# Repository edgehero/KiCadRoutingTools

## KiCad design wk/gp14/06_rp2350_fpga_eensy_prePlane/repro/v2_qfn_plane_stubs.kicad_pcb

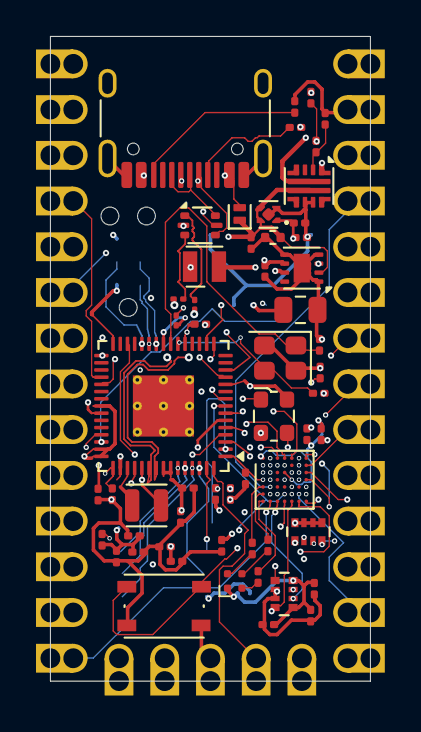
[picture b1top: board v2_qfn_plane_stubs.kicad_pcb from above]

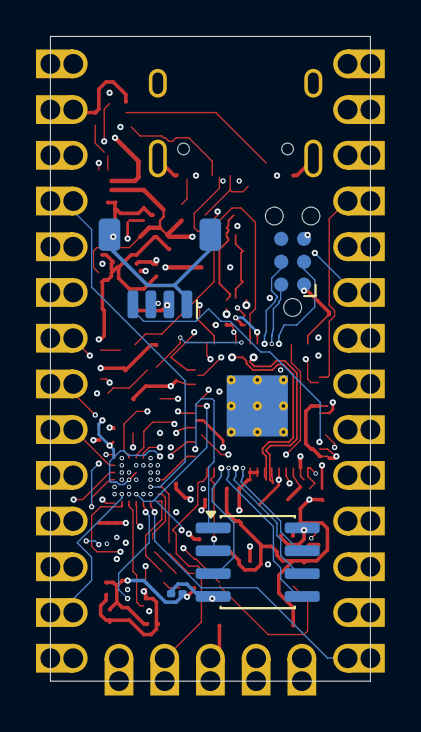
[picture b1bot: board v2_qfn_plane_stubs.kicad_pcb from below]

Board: 6 copper layers, 17.8 x 35.8 mm, 61 parts (4 on the bottom side), 74 nets.

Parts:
C1, C2, C3, C7, C8, C9, C10, C11, C12, C17, C18, C20, C21, C23, C24, C25, C28, C29, C30: 1uF; C_0201_0603Metric
C5, C13, C16, C19, C22: 4.7uF; C_0201_0603Metric
C6: 4.7uF; amemb-C_0201_0603Metric_L
C14, C15: 18pF; C_0201_0603Metric
C26: 10uF; amemb-C_0402_1005Metric_L
C27: 22uF; C_0805_2012Metric
D1: LED; LED_Wurth_150044M155260
D2: D_Schottky_Small; D_SOD-882
J1: USB_C_Receptacle_USB2.0_14P; USB_C_Receptacle_HRO_TYPE-C-31-M-12-Edge_Silkscreen_Removed
J2: Conn_ARM_SWD_TagConnect_TC2030-NL; Tag-Connect_TC2030-IDC-NL_2x03_P1.27mm_Vertical
J3: Conn_01x04_MountingPin; JST_SH_SM04B-SRSS-TB_1x04-1MP_P1.00mm_Horizontal
L1: 3.3uH; L_Wuerth_PMCI-201610
L2: 2.2uH; L_Wurth_WE-LQSH-2010
R1, R2: 5.1kR; R_0201_0603Metric
R3: 33R; R_0201_0603Metric
R4, R5: 27R; amemb-R_0201_0603Metric_L
R6: 1MR; R_0201_0603Metric
R7: 680R; R_0201_0603Metric
R8: 360R; R_0201_0603Metric
R9: 300R; R_0201_0603Metric
R11: 470kR; R_0201_0603Metric
R12: 18.7kR; R_0201_0603Metric
R13: 46.4kR; R_0201_0603Metric
RN1, RN2: 10kR; R_Array_Convex_4x0402
SW1: SKRPADE010; SW_Push_1P1T_NO_Vertical_Wuerth_434133025816
U1: APS1604M-SQR-SN; SOIC-8_3.9x4.9mm_P1.27mm
U2: T8F49I2X; amemb-WLCSP-49_3x3mm_Layout7x7_P0.4mm_Ball0.25mm
U3: USBLC6-2P6; SOT-666
U4: TPS7A2011DQN; Texas_X2SON-4_1x1mm_P0.65mm
U5: LM73100RPWR; Texas_Instruments-VQFN-HR-10_2x2mm_P0.475mm
U6: RP2354A; QFN-60-1EP_7x7mm_P0.4mm_EP3.4x3.4mm_ThermalVias
U7: TPS62162DSG; WSON-8-1EP_2x2mm_P0.5mm_EP0.9x1.6mm
U8: Teensy4.0; Teensy40
Y1: 12MHZ; Crystal_SMD_2520-4Pin_2.5x2.0mm
Y2: 32MHz; Oscillator_SMD_ECS_2520MV-xxx-xx-4Pin_2.5x2.0mm

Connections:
+1V1: C3.1, C16.1, C17.1, C18.1, U2.A1 (VCCA_PLL), U2.C4 (VCC), U2.D5 (VCC), U4.1 (OUT), U7.3 (EN)
+3V3: C2.1, C7.1, C8.1, C9.1, C10.1, C11.1, C12.1, C13.1, C19.1, C20.1, C21.1, C22.1, C23.1, C24.1, C25.1, C27.1, D1.1 (A), J2.1 (VCC), J3.2, L2.2, R3.2, RN1.5 (R4.2), RN1.6 (R3.2), RN1.7 (R2.2), RN1.8 (R1.2), RN2.5 (R4.2), RN2.8 (R1.2), U1.8 (VDD), U2.B2 (VCCIO1B), U2.B6 (VCCIO2A), U2.D1 (VCCIO1A), U2.F7 (VCCIO2B), U6.1 (IOVDD), U6.11 (IOVDD), U6.20 (IOVDD), U6.30 (IOVDD), U6.38 (IOVDD), U6.44 (ADC_AVDD), U6.45 (IOVDD), U6.49 (VREG_VIN), U6.53 (USB_OTP_VDD), U6.54 (QSPI_IOVDD), U7.6 (VOS), U8.16 (3V3), U8.31 (3V3), Y2.4 (VDD)
/PIO22: U6.34 (GPIO22), U8.4 (PIN2)
/PIO23: U6.35 (GPIO23), U8.5 (PIN3)
/Power Supply and USB/D+: R4.1, U3.1 (I/O1)
/Power Supply and USB/D-: R5.1, U3.3 (I/O2)
/RP2354A/1V1: C6.1, C28.1, C29.1, C30.1, L1.1, U6.6 (DVDD), U6.23 (DVDD), U6.39 (DVDD), U6.50 (VREG_FB)
/RP2354A/FPGA.CLK: U2.F3 (GPIOL_02_CCK), U6.4 (GPIO2)
/RP2354A/FPGA.DONE: RN2.1 (R1.1), U2.F4 (CDONE), U6.8 (GPIO5)
/RP2354A/FPGA.MOSI: U2.F2 (GPIOL_04_CDI0), U6.5 (GPIO3)
/RP2354A/FPGA.OSC_EN: R6.1, U6.31 (GPIO19), Y2.1 (Tri-State)
/RP2354A/FPGA.~CS: RN2.6 (R3.2), U2.G3 (~GPIOL_01_SS), U6.3 (GPIO1)
/RP2354A/FPGA.~RESET: RN2.7 (R2.2), U2.G4 (~CRESET), U6.7 (GPIO4)
/RP2354A/FPGA.~STATUS: U2.A4 (GPIOL_21_~STATUS), U6.9 (GPIO6)
/RP2354A/ON/OFF: U6.28 (GPIO17), U8.19 (ON/OFF)
/RP2354A/PROGRAM: U6.60 (QSPI_SS), U8.18 (PROGRAM)
/RP2354A/QSPI_PSRAM_~CS: U1.1 (~CE), U6.2 (GPIO0)
/RP2354A/RP.UART0_RX: U6.17 (GPIO13), U8.10 (PIN8)
/RP2354A/RP.UART0_TX: U6.16 (GPIO12), U8.9 (PIN7)
/RP2354A/RP.UART1_RX: U6.12 (GPIO8), U8.2 (PIN0)
/RP2354A/RP.UART1_TX: U6.13 (GPIO9), U8.3 (PIN1)
/RP2354A/SCL: J3.4, U6.43 (GPIO29/ADC3)
/RP2354A/SDA: J3.3, U6.42 (GPIO28/ADC2)
/RP2354A/SWCLK: J2.4 (SWCLK), U6.24 (SWCLK)
/RP2354A/SWDIO: J2.2 (SWDIO), U6.25 (SWDIO)
/RP2354A/USB_D+: R4.2, U6.52 (USB_DP)
/RP2354A/USB_D-: R5.2, U6.51 (USB_DM)
/T8F49I2X/B: R9.2, U2.G1 (GPIOL_05_CDI5)
/T8F49I2X/G: R8.2, U2.F1 (GPIOL_06_CDI1)
/T8F49I2X/PIN.4: U2.A5 (GPIOR_05), U8.6 (PIN4)
/T8F49I2X/PIN.5: RN1.4 (R4.1), U2.D7 (GPIOR_17_CTRL6_CBUS2), U8.7 (PIN5)
/T8F49I2X/PIN.6: RN1.3 (R3.1), U2.C7 (GPIOR_16_CTRL7_CBUS1), U8.8 (PIN6)
/T8F49I2X/PIN.9: RN1.2 (R2.1), U2.D6 (GPIOR_15_CBUS0), U8.11 (PIN9)
/T8F49I2X/PIN.10: RN1.1 (R1.1), U2.G7 (~GPIOR_37_TEST), U8.12 (PIN10)
/T8F49I2X/PIN.11: RN2.4 (R4.1), U2.G5 (GPIOR_34_CSI), U8.13 (PIN11)
/T8F49I2X/PIN.12: U2.G2 (GPIOL_03_CDI4), U8.14 (PIN12)
/T8F49I2X/PIN.13: U2.F5 (GPIOR_24), U8.20 (PIN13)
/T8F49I2X/PIN.14: U2.F6 (GPIOR_26_CBSEL0), U8.21 (PIN14)
/T8F49I2X/PIN.15: U2.E5 (GPIOR_23_CTRL4), U8.22 (PIN15)
/T8F49I2X/PIN.16: U2.C6 (GPIOR_13), U8.23 (PIN16)
/T8F49I2X/PIN.17: U2.B3 (GPIOL_16_CLK2), U8.24 (PIN17)
/T8F49I2X/PIN.18: U2.B7 (GPIOR_10), U8.25 (PIN18)
/T8F49I2X/PIN.19: U2.A7 (GPIOR_07), U8.26 (PIN19)
/T8F49I2X/PIN.20: U2.A3 (GPIOL_18_CTRL2), U8.27 (PIN20)
/T8F49I2X/PIN.21: U2.C2 (GPIOL_12_CTRL0), U8.28 (PIN21)
/T8F49I2X/PIN.22: U2.D2 (GPIOL_11_CDI3), U8.29 (PIN22)
/T8F49I2X/PIN.23: U2.E2 (GPIOL_09_CDI2), U8.30 (PIN23)
/T8F49I2X/R: R7.2, U2.E1 (GPIOL_10_CDI7)
/VIN: R11.1, U5.5 (IN), U8.33 (VIN)
GND: C1.2, C2.2, C3.2, C5.2, C6.2, C7.2, C8.2, C9.2, C10.2, C11.2, C12.2, C13.2, C14.2, C15.2, C16.2, C17.2, C18.2, C19.2, C20.2, C21.2, C22.2, C23.2, C24.2, C25.2, C26.2, C27.2, C28.2, C29.2, C30.2, J1.A1 (GND), J1.A12 (GND), J1.B1 (GND), J1.B12 (GND), J1.SH (SHIELD), J2.5 (GND), J3.1, J3.MP (MountPin), R1.2, R2.2, R6.2, R13.2, RN2.2 (R2.1), RN2.3 (R3.1), SW1.2, U1.4 (VSS), U2.A2 (GND), U2.A6 (GND), U2.B1 (GND), U2.C1 (GND), U2.C5 (GND), U2.D4 (GND), U2.E7 (GND), U3.2 (GND), U4.2 (GND), U4.5 (Pad), U5.8 (GND), U5.9 (IMON), U6.47 (VREG_PGND), U6.61 (GND), U7.1 (PGND), U7.4 (AGND), U7.5 (FB), U7.9 (PAD), U8.1 (GND), U8.17 (GND), U8.32 (GND), Y1.2 (G), Y1.4 (G), Y2.2 (GND)
unnamed: D1.4 (BK), R9.1
unnamed: D1.3 (GK), R8.1
unnamed: D1.2 (RK), R7.1
unnamed: D2.2 (A), J1.A4 (VBUS), J1.A9 (VBUS), J1.B4 (VBUS), J1.B9 (VBUS)
unnamed: C1.1, C26.1, D2.1 (K), U3.5 (VBUS), U4.3 (EN), U4.4 (IN), U5.6 (OUT), U7.2 (VIN)
unnamed: J1.A5 (CC1), R1.1
unnamed: J1.B5 (CC2), R2.1
unnamed: J1.A6 (D+), J1.B6 (D+), U3.6 (I/O1)
unnamed: J1.A7 (D-), J1.B7 (D-), U3.4 (I/O2)
unnamed: J2.3 (~RESET), U6.26 (RUN)
unnamed: U1.6 (SCLK), U6.56 (QSPI_SCLK)
unnamed: U1.3 (SIO2), U6.58 (QSPI_SD2)
unnamed: U1.7 (SIO3), U6.55 (QSPI_SD3)
unnamed: U1.5 (SI/SIO0), U6.57 (QSPI_SDO)
unnamed: U1.2 (SO/SIO1), U6.59 (QSPI_SD1)
unnamed: U2.B4 (GPIOL_20_PLLIN), Y2.3 (OUT)
unnamed: SW1.1, U2.G6 (GPIOR_35_CSO)
unnamed: R11.2, R12.1, U5.1 (EN/UVLO)
unnamed: R12.2, R13.1, U5.2 (OVLO)
unnamed: C5.1, R3.1, U6.46 (VREG_AVDD)
unnamed: L1.2, U6.48 (VREG_LX)
unnamed: C14.1, U6.21 (XIN), Y1.3
unnamed: C15.1, U6.22 (XOUT), Y1.1
unnamed: L2.1, U7.7 (SW)

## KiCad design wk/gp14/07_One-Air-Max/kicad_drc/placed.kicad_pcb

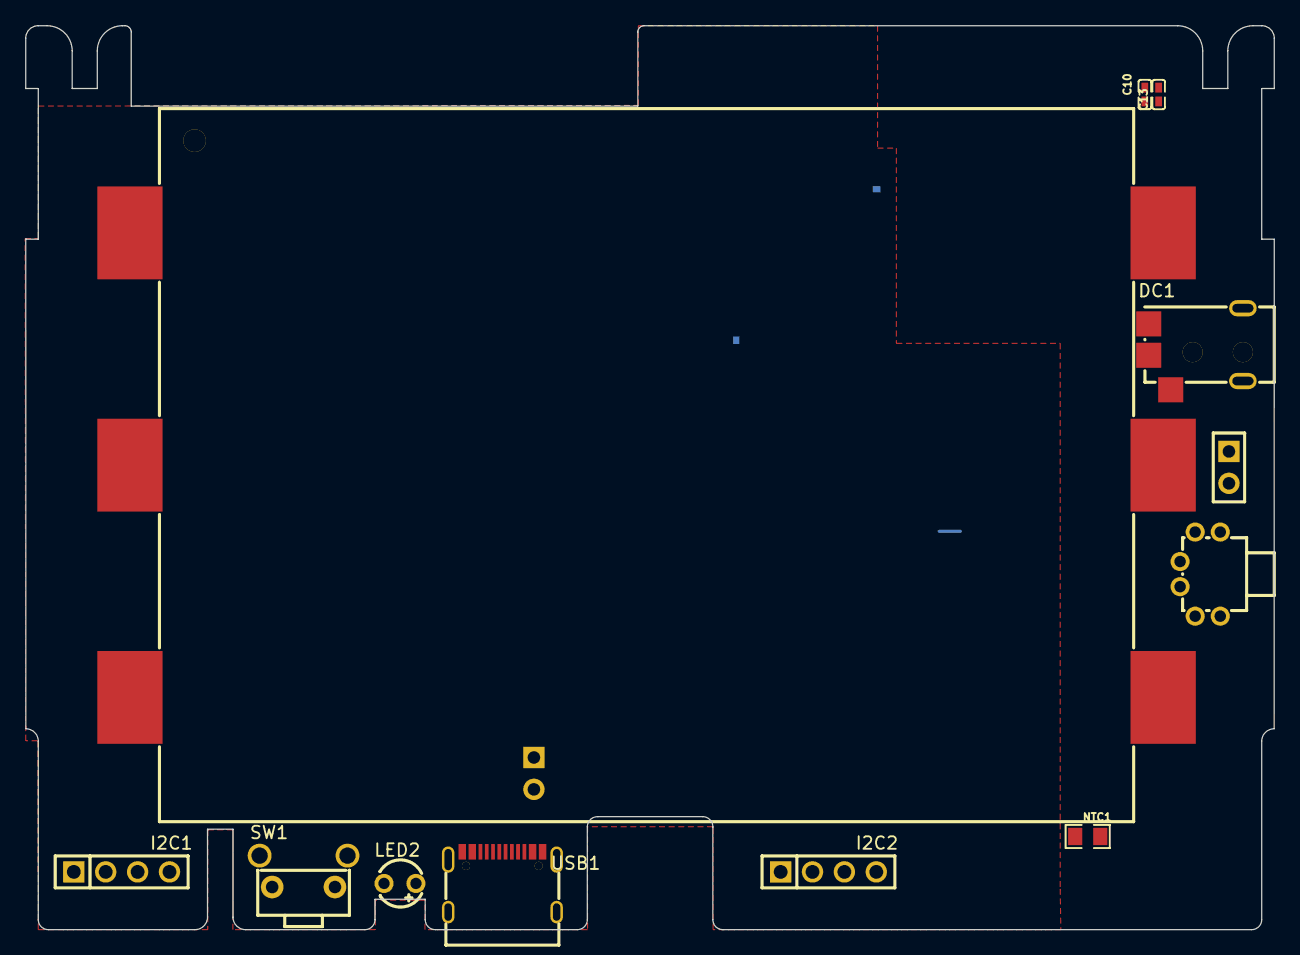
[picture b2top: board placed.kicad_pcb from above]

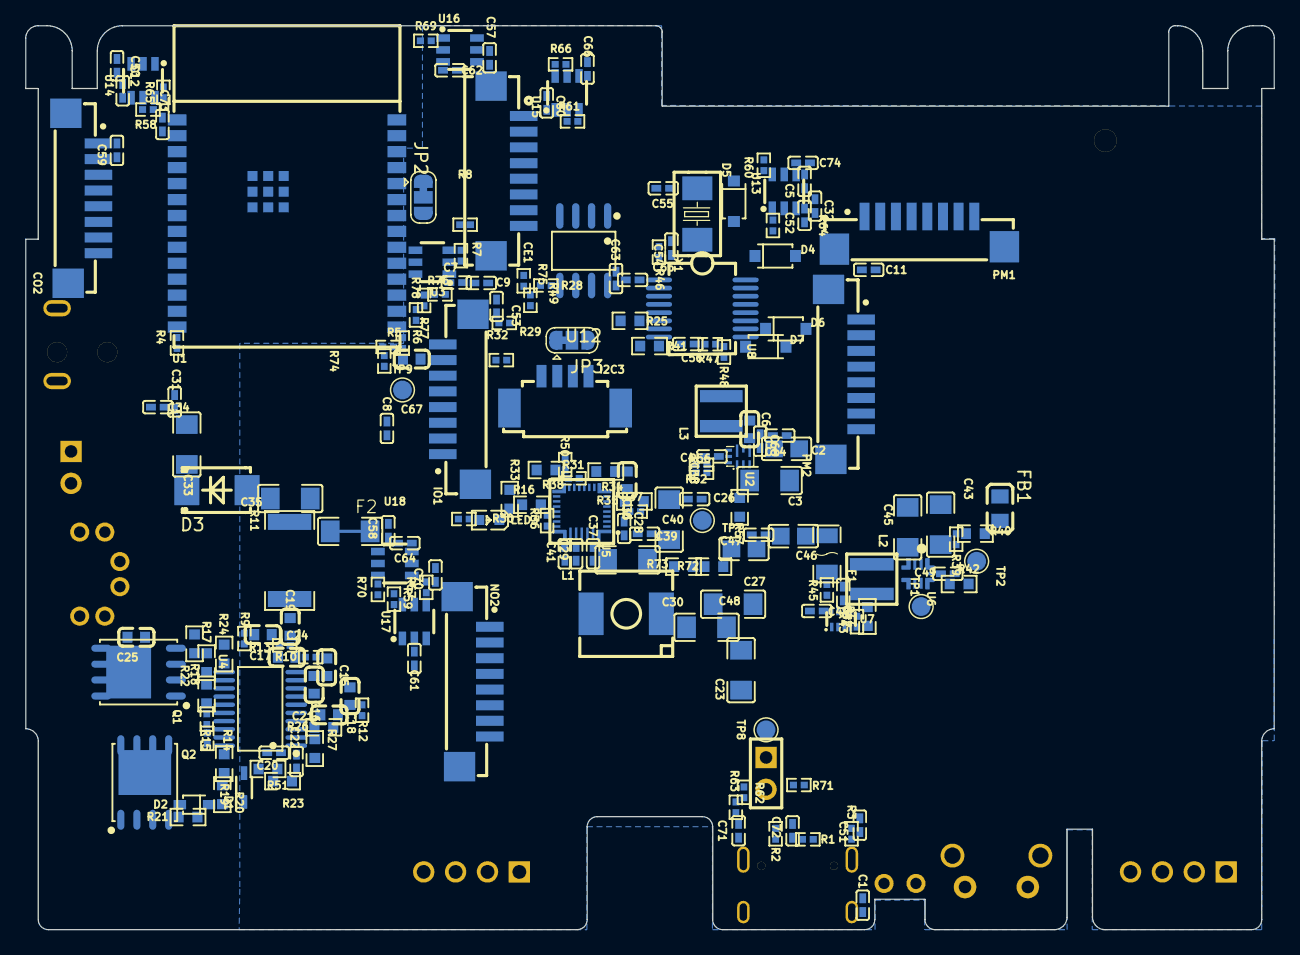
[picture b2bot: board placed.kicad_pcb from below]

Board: 4 copper layers, 99.5 x 72.0 mm, 204 parts (192 on the bottom side), 120 nets, no tracks yet.

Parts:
BAT1: BH-18650-B5BA016; BAT-SMD_BH-18650-B5BA016
Battery1: ZX-PM2.54-1-2PY; HDR-TH_2P-P2.54-V-F
C1, C5, C7, C9, C10, C11, C12, C13, C26, C31, C34, C37, C39, C42, C44, C47, C50, C51, C52, C53, C56, C63, C65, C70: 0.1uF; C0402
C2: 10uF/25V; C0805
C3: 22uF/16V; C1206
C4, C49: 3.3nF; C0402
C6: 22uF; C0603
C8: 10nF; C0402
C14, C57, C58, C68, C74: 22uF; C0402
C15, C16, C17, C18, C19, C21, C24, C25: 0.1uF/50V; C0603
C20, C22: 1uF/50V; C0402
C23, C27, C30, C33, C35, C38, C40, C43, C45: 10uF; C1206
C28, C29: 47nF; C0402
C32, C59, C60, C61, C62, C64: 2.2uF; C0402
C36: 4.7uF; C0603
C41, C71, C72: 1nF; C0402
C46, C48: 22uF; C0805
C54, C55: 22pF_NM; C0402
C66, C73: 1uF; C0402
C67: 500pF; C0603
CE1: HC-1.25-8PWT; CONN-SMD_HC-1.25-8PWT
CO2: HC-1.25-8PLT; CONN-SMD_8P-P1.25_HC-1.25-8PLT
D1: BAS16J_135; SOD2512X80N
D2: MMSZ5246BS-7-F; SOD-323_L1.8-W1.3-LS2.5-RD
D3: SMBJ24A_C908801; SMB_L4.4-W3.6-LS5.3-RD
D4, D5, D6, D7: B5817W_C7420328; SOD-123_L2.7-W1.6-LS3.7-FD
DC1: DC-045A-13A; DC-IN-SMD_DC-045A-13A
F1: 2A-16V; F1206
F2: Fuse 5A; PCB_fuse
FB1: PBY201209T-601Y-N; L0805
I2C1, I2C2: Conn_01x04; HDR-TH_4P-P2.54-V-F
I2C3: 1.25-4PWB; CONN-SMD_1.25-4PWB
IO1: HC-1.25-8PLT; CONN-SMD_8P-P1.25_HC-1.25-8PLT
JP2, JP3: SolderJumper_3_Bridged12; SolderJumper-3_P1.3mm_Bridged12_RoundedPad1.0x1.5mm
L1: SPM6530T-1R0M120; IND-SMD_L7.1-W6.5-P5.60
L2: XGL4020-102MEC; IND-SMD_L4.0-W4.0_XAL4030-332MEC
L3: YSMC0420V-1R0M; IND-SMD_L4.0-W4.0_XGL4020
LED2: XL-304UBC; LED-TH_BD3.8-P2.54-FD_BLUE
LED3: FC-DA1608HRK-620D; LED0603-RD_RED
NO2: HC-1.25-8PLT; CONN-SMD_8P-P1.25_HC-1.25-8PLT
NTC1: KNTC0805/10KF3950; R0805
PM1, PM2: HC-1.25-8PLT; CONN-SMD_8P-P1.25_HC-1.25-8PLT
PWR_SW1: TK-6580A8-1; SW-TH_TK-6580A8-1
Q1, Q2: CSD18534Q5A; PQFN-8_L5.8-W4.9-P1.27-LS6.0-BL
R1, R2, R48: 5.1K; R0402
R3, R6, R31, R37: 100K; R0402
R4, R5, R8, R28, R29, R30, R32, R45, R47, R49, R50, R58, R59, R60, R61, R64, R65, R66, R67, R69, R70, R74, R75, R76, R77, R78: 10K; R0402
R7: 51K; R0402
R9, R12, R14, R15: 1K; R0402
R10, R13, R36: 100; R0402
R11: 10m / 1W; R2512
R16: 10.5K; R0603
R17, R19: 5.1K; R0603
R18: 10M; R0603
R20: 1M; R0603
R21: 3M; R0603
R22: 10K; R0603
R23, R25, R26, R27, R33, R41, R51, R72, R73: 0; R0603
R24: 470K; R0603
R34: 5.23K; R0603
R35: 255K; R0603
R38: 30.1K; R0603
R39: 200K; R0402
R40: 27K; R0603
R42, R57: 7.15K; R0603
R43: 16.9K; R0402
R44: 5K; R0603
R46: 1M; R0402
R52: 113k; R0402
R56: 24.9k; R0402
R62, R63: 22; R0402
R71: 210; R0402
SW1: TS-1096-A1B2-D2; KEY-TH_TS-1096-A1B2-D2
Solarpower1: ZX-PM2.54-1-2PY; HDR-TH_2P-P2.54-V-F
TP1, TP2, TP7, TP8, TP9: T_PG; TestPoint_Pad_D1.5mm
U1: ESP32-C6-WROOM-1-N8; WIRELM-SMD_ESP32-C6-WROOM-1
U2: TPS62902RPJR; VQFN-HR-9_L2.0-W1.5-P0.50-TL
U3: TPL5010DDCR; SOT-23-6_L2.9-W1.6-P0.95-LS2.8-BR
U4: BQ7790512PWR; TSSOP-20_L6.5-W4.4-P0.65-LS6.4-BL
U5: BQ25672RQMR; VQFN-29_L4.0-W4.0-P0.40-BL
U6: TPS62903QRYTRQ1_C20345985; VQFNHR-9_L2.2-W2.0_TPS62993QRYTRQ1
U7: TPS2117DRLR_C22399676; SOT-583-8_L2.1-W1.2-P0.50-LS1.6-BL
U8: WK2132-ISSG; SSOP-16_L7.2-W5.3-P0.65-LS7.8-BL
U12: AT24CM02-SSHD-B; SOIC-8_L4.9-W3.9-P1.27-LS6.0-BL
U13, U14, U15, U16, U17, U18: TPS27081ADDCR; SOT-23-6_L2.9-W1.6-P0.95-LS2.8-BR
USB1: GT-USB-7010ASV; USB-C-SMD_G-SWITCH_GT-USB-7010ASV
X1: SMD-5032_2P 14.7456MHZ 20PF 20PPM; OSC-SMD_L5.0-W3.2

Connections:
+3V3: C3.2, C6.2, C7.2, C9.1, C10.2, C13.2, C53.2, C63.2, C65.2, C66.2, C70.2, C73.2, I2C1.1, I2C2.1, I2C3.1, IO1.3, L3.1, R4.2, R5.2, R6.1, R8.2, R28.2, R29.2, R32.2, R47.2, R48.1, R49.2, R52.2, R66.2, R67.2, R74.2, R75.2, R76.2, R77.2, R78.2, U1.2 (3V3), U2.3 (VOS), U3.1 (VDD), U8.1 (VCC), U12.8 (VCC), U15.4 (VIN), U17.4 (VIN)
+5V: C2.1, C5.2, C14.2, C50.2, C57.2, C58.2, C68.2, C74.2, F1.1, IO1.1, R45.2, R64.2, R65.2, R69.2, R70.2, U2.5 (EN), U2.6 (VIN), U13.4 (VIN), U14.4 (VIN), U16.4 (VIN), U18.4 (VIN)
+5VBAT: C42.2, C43.2, C44.2, C45.2, L2.1, R39.2, U6.3 (VOS), U7.6 (VIN2)
+5VUSB: R43.2, U7.3 (VIN1), U7.5 (MODE), USB1.A4B9 (VBUS), USB1.B4A9 (VBUS)
/A0: R25.1, U8.6 (MP1)
/A1: R41.1, U8.4 (MP3)
/BOOT: C8.2, R5.1, SW1.1, U1.15 (IO9)
/Battery_holder/AVDD: C22.2, R23.2, U4.2 (AVDD)
/Battery_holder/BAT1: BAT1.2, BAT1.4, R9.1
/Battery_holder/BAT2: BAT1.3, BAT1.5, R12.1
/Battery_holder/BAT_TH: NTC1.2, R22.1, U4.15 (TS)
/Battery_holder/CHG: R19.2, U4.13 (CHG)
/Battery_holder/CTRC: R26.1, U4.18 (CTRC)
/Battery_holder/CTRD: R27.2, U4.19 (CTRD)
/Battery_holder/DSG: R17.2, U4.11 (DSG)
/Battery_holder/LD: R24.2, U4.14 (LD)
/Battery_holder/SRN: C17.1, C19.2, R13.2, U4.10 (SRN)
/Battery_holder/SRP: C15.2, C17.2, R10.2, U4.9 (SRP)
/Battery_holder/VBAT+: BAT1.6, C25.2, PWR_SW1.4, PWR_SW1.6, R14.1, R15.1
/EN: C67.2, R6.2, TP9.1, U1.3 (EN), U3.6 (RSTn)
/EN_CE: CE1.5, R61.2, U1.23 (IO15), U15.5 (ON/OFF), U16.5 (ON/OFF)
/EN_CO2: R58.2, U1.5 (IO5), U14.5 (ON/OFF)
/EN_NO2: R59.2, U1.4 (IO4), U17.5 (ON/OFF), U18.5 (ON/OFF)
/EN_PM: R60.2, U1.26 (IO3), U13.5 (ON/OFF)
/I2C_~RST: C56.2, R47.1, U8.8 (#RSTN)
/IO18: IO1.6, R78.1, U1.16 (IO18)
/IO19: IO1.5, R77.1, U1.17 (IO19)
/IO20: IO1.4, R76.1, U1.18 (IO20)
/IO21: CE1.6, R75.1, U1.19 (IO21)
/IO22: R74.1, U1.20 (IO22)
/IO23: CE1.4, R8.1, U1.21 (IO23)
/LED: R71.2, U1.11 (IO10)
/PM1_RXD: D5.2 (K), PM1.5
/PM1_TXD: D4.1 (A), PM1.4
/PM2_RXD: D7.2 (K), PM2.5
/PM2_TXD: D6.1 (A), PM2.4
/PR1: R43.1, R44.2, U7.4 (PR1)
/RX_CE: JP3.1 (A), U1.24 (RXD0)
/RX_CO2: CO2.5, U1.8 (IO0)
/SCL: I2C1.3, I2C2.3, I2C3.3, IO1.7, JP2.3 (B), NO2.7, R28.1, R32.1, U1.6 (IO6), U5.14 (SCL), U8.5 (MP2), U12.6 (SCL)
/SCL_TXD: CE1.7, JP2.2 (C)
/SDA: I2C1.4, I2C2.4, I2C3.4, IO1.8, JP3.3 (B), NO2.8, R29.1, R49.1, U1.7 (IO7), U5.15 (SDA), U8.7 (MP0), U12.5 (SDA)
/SDA_RXD: CE1.8, JP3.2 (C)
/Solar_module/BTST1: C28.2, U5.4 (BTST1)
/Solar_module/BTST2: C29.2, U5.19 (BTST2)
/Solar_module/FB/VSET: R39.1, R40.2, TP2.1, U6.9 (FB/VSET)
/Solar_module/ILIM_HIZ: R35.2, R37.2, U5.17 (ILIM_HIZ)
/Solar_module/PROG: R16.2, U5.20 (PROG)
/Solar_module/REGN: C36.2, R34.1, R35.1, U5.5 (REGN)
/Solar_module/SW1: C28.1, L1.1, U5.28 (SW1)
/Solar_module/SW2: C29.1, L1.2, U5.26 (SW2)
/Solar_module/SYS: C26.2, C27.2, R72.1, TP7.1, U5.25 (SYS)
/Solar_module/Solar+: C31.2, C33.2, C34.2, C35.2, D3.1, DC1.1, R30.1, Solarpower1.1, U5.2 (VBUS), U5.3 (VBUS), U5.8 (VAC2), U5.9 (VAC1)
/Solar_module/VBAT: Battery1.1, C23.2, C30.2, F2.1, R36.2, R73.1, TP8.1, U5.22 (BAT), U5.23 (BAT)
/TX_CE: JP2.1 (A), U1.25 (TXD0)
/TX_CO2: CO2.4, U1.9 (IO1)
/USB+: R63.2, U1.14 (IO13)
/USB-: R62.2, U1.13 (IO12)
/USB_D+: C71.2, R63.1, USB1.A6 (DP1), USB1.B6 (DP2)
/USB_D-: C72.2, R62.1, USB1.A7 (DN1), USB1.B7 (DN2)
/VMUX: F1.2, U7.2 (VOUT), U7.7 (VOUT)
/VOUT1: C11.2, C32.2, C52.2, PM1.1, PM2.1, U13.2 (VOUT), U13.3 (VOUT)
/VOUT2: C12.2, C59.2, CO2.1, U14.2 (VOUT), U14.3 (VOUT)
/VOUT3: C60.2, CE1.3, U15.2 (VOUT), U15.3 (VOUT)
/VOUT4: C62.2, CE1.1, U16.2 (VOUT), U16.3 (VOUT)
/VOUT5: C61.2, NO2.3, U17.2 (VOUT), U17.3 (VOUT)
/VOUT6: C64.2, NO2.1, U18.2 (VOUT), U18.3 (VOUT)
/WD_RST: U1.27 (IO2), U3.4 (DONE)
BAT-: BAT1.1, C15.1, C16.1, C18.1, C19.1, C20.1, C21.1, C22.1, NTC1.1, R10.1, R11.1, R26.2, R27.1, R51.1, U4.8 (AVSS), U4.20 (DVSS)
GND: C1.1, C2.2, C3.1, C4.1, C5.1, C6.1, C7.1, C8.1, C9.2, C10.1, C11.1, C12.1, C13.1, C14.1, C32.1, C50.1, C51.1, C52.1, C53.1, C54.1, C55.1, C56.1, C57.1, C58.1, C59.1, C60.1, C61.1, C62.1, C63.1, C64.1, C65.1, C66.1, C67.1, C68.1, C70.1, C71.1, C72.1, C73.1, C74.1, CE1.2, CE1.9, CE1.10, CO2.2, CO2.10, FB1.1, I2C1.2, I2C2.2, I2C3.2, I2C3.5, IO1.2, IO1.9, IO1.10, LED2.2 (K), NO2.2, NO2.9, NO2.10, PM1.2, PM1.10, PM2.2, PM2.9, PM2.10, R1.1, R2.1, R3.1, R7.1, R25.2, R41.2, R44.1, R56.1, R57.1, R58.1, R59.1, R60.1, R61.1, SW1.2, U1.1 (GND), U1.28 (GND), U1.29 (GND), U1.30 (GND), U1.31 (GND), U1.32 (GND), U1.33 (GND), U1.34 (GND), U1.35 (GND), U1.36 (GND), U1.37 (GND), U2.4 (GND), U3.2 (GND), U7.1 (GND), U8.12 (GND), U8.13 (MD0), U12.3 (A2), U12.4 (GND), U12.7 (WP), U13.1 (R2), U14.1 (R2), U15.1 (R2), U16.1 (R2), U17.1 (R2), U18.1 (R2), USB1.A1B12 (GND), USB1.B1A12 (GND)
unnamed: C1.2, R3.2, USB1.1 (SHELL), USB1.2 (SHELL), USB1.3 (SHELL), USB1.4 (SHELL)
unnamed: C24.2, Q1.1 (S), Q1.2 (S), Q1.3 (S), R11.2, R13.1, R18.1
unnamed: D1.2, R19.1, R20.2
unnamed: D1.1, D2.1 (K), Q2.4 (G), R20.1, R21.2
unnamed: D4.2 (K), U8.15 (TX1)
unnamed: D5.1 (A), U8.16 (RX1)
unnamed: D6.2 (K), U8.10 (TX2)
unnamed: D7.1 (A), U8.11 (RX2)
unnamed: F2.2, PWR_SW1.2, PWR_SW1.5
unnamed: C51.2, LED2.1 (A), R71.1
unnamed: LED3.2 (A), R30.2
unnamed: LED3.1 (K), U5.1 (STAT)
unnamed: Q1.5 (D), Q1.6 (S), Q1.7 (S), Q1.8 (S), Q2.5 (D), Q2.6 (S), Q2.7 (S), Q2.8 (S)
unnamed: Q1.4 (G), R17.1, R18.2
unnamed: R16.1, R33.1
unnamed: R4.1, U1.10 (IO8)
unnamed: R52.1, R56.2, U2.9 (FB/VSET)
unnamed: R57.2, U2.7 (MODE/S-CONF)
unnamed: C4.2, U2.8 (SS/TR)
unnamed: L3.2, U2.2 (SW)
unnamed: R7.2, U3.3 (DELAY/M_RST)
unnamed: R23.1, R51.2, U4.17 (CCFG)
unnamed: C16.2, R9.2, U4.7 (VC1)
unnamed: C18.2, R12.2, U4.6 (VC2)
unnamed: C21.2, R15.2, U4.3 (VC5), U4.4 (VC4), U4.5 (VC3)
unnamed: C20.2, R14.2, U4.1 (VDD)
unnamed: R22.2, U4.16 (VTB)
unnamed: R36.1, U5.18 (BATP)
unnamed: R31.1, U5.13 (CE)
unnamed: C37.2, C38.2, C39.2, C40.2, U5.29 (PMID)
unnamed: C41.1, U5.24 (SDRV)
unnamed: R34.2, R38.1, R50.2, U5.16 (TS)
unnamed: C46.2, C47.2, C48.2, R72.2, R73.2, U6.5 (EN), U6.6 (VIN)
unnamed: R42.2, U6.7 (MODE/S-CONF)
unnamed: TP1.1, U6.1 (PG)
unnamed: C49.2, U6.8 (SS/TR)
unnamed: L2.2, U6.2 (SW)
unnamed: R45.1, U7.8 (ST)
unnamed: R48.2, U8.9 (#IRQ)
unnamed: C54.2, R46.2, U8.2 (OSCI), X1.2 (OSC2)
unnamed: C55.2, R46.1, U8.3 (OSCO), X1.1 (OSC1)
unnamed: R64.1, U13.6 (R1/C1)
unnamed: R65.1, U14.6 (R1/C1)
unnamed: R66.1, U15.6 (R1/C1)
unnamed: R69.1, U16.6 (R1/C1)
unnamed: R67.1, U17.6 (R1/C1)
unnamed: R70.1, U18.6 (R1/C1)
unnamed: R1.2, USB1.A5 (CC1)
unnamed: R2.2, USB1.B5 (CC2)
PGND: Battery1.2, C23.1, C24.1, C25.1, C26.1, C27.1, C30.1, C31.1, C33.1, C34.1, C35.1, C36.1, C37.1, C38.1, C39.1, C40.1, C41.2, C42.1, C43.1, C44.1, C45.1, C46.1, C47.1, C48.1, C49.1, D2.2 (A), D3.2, DC1.2, DC1.3, DC1.4, FB1.2, Q2.1 (S), Q2.2 (S), Q2.3 (S), R21.1, R24.1, R31.2, R33.2, R37.1, R38.2, R40.1, R42.1, R50.1, Solarpower1.2, U5.10 (ACDRV2), U5.11 (ACDRV1), U5.27 (GND), U6.4 (GND)
